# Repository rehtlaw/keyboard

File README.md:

## Build

- make sure `node` and `npm` are installed and up to date
- clone the repo
- run `npm install` inside the repo
- run `npm run gen` to regenerate the pcb file

## quirks

Ergogen's fillets are a little silly and will depending on your settings create little circles around some corners of your outline.
There doesn't seem to be any problem with just deleting them in KiCAD after the PCB generation, so just do that after running 
the generator.

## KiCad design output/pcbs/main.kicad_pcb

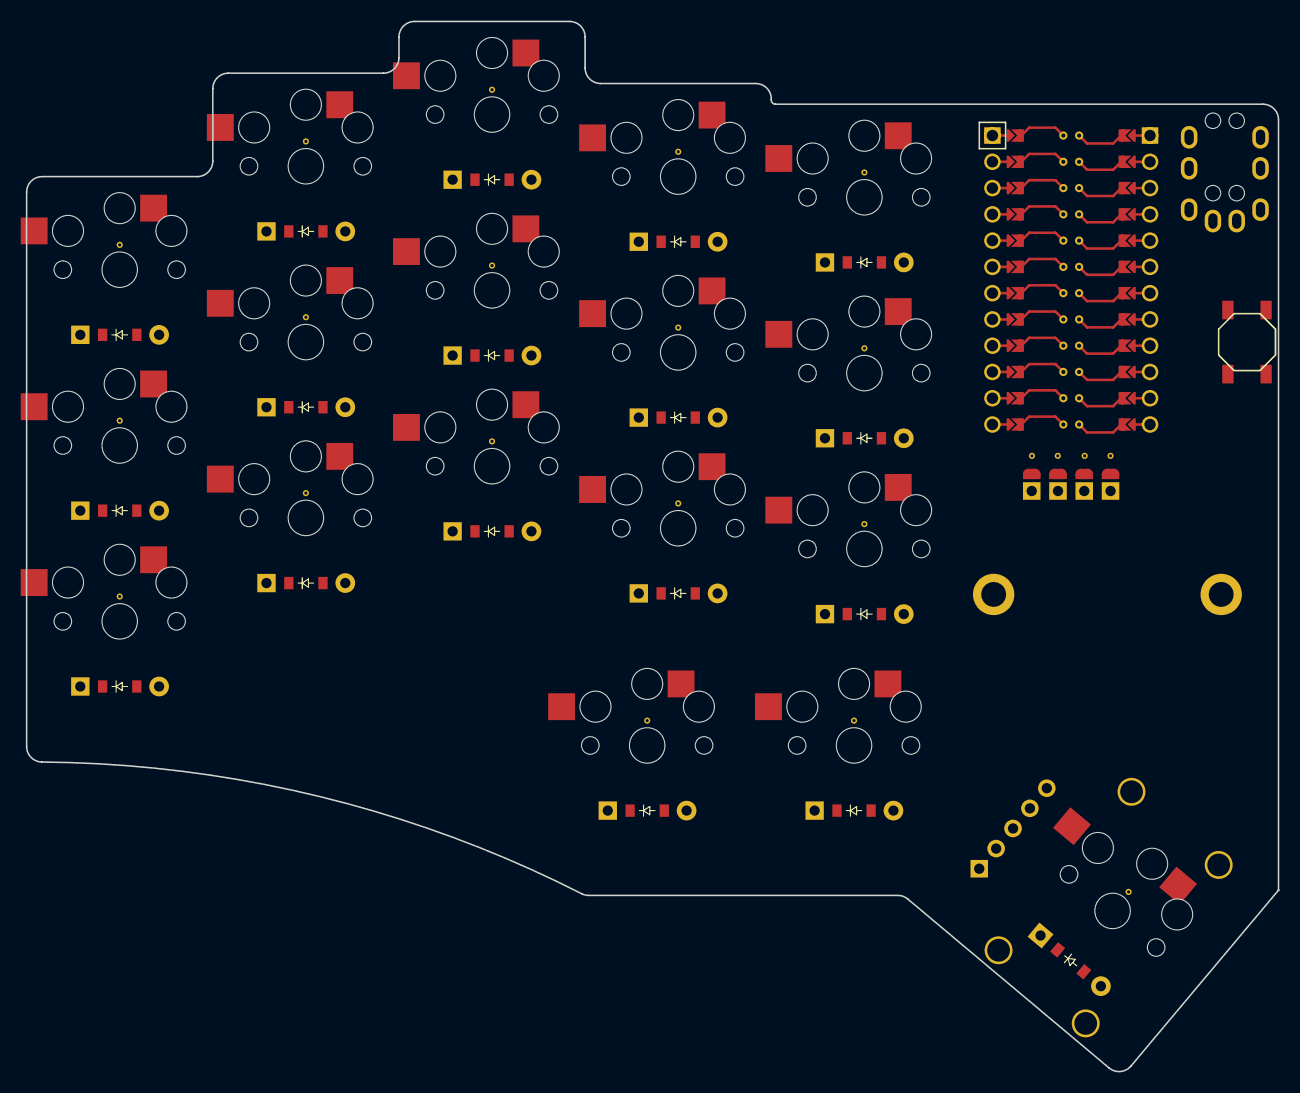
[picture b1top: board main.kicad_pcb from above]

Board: 2 copper layers, 121.0 x 101.5 mm, 44 parts (0 on the bottom side), 33 nets, no tracks yet.

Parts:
B1, B2: SW_TACT_ALPS_SKQGABE010
D1, D2, D3, D4, D5, D6, D7, D8, D9, D10, D11, D12, D13, D14, D15, D16, D17, D18: ComboDiode
Mount1: TH1; MountingHole_2.2mm_M2_DIN965_Pad
Mount2: TH2; MountingHole_2.2mm_M2_DIN965_Pad
S1, S2, S3, S4, S5, S6, S7, S8, S9, S10, S11, S12, S13, S14, S15, S16, S17, S18: PG1350
TRRS1: TRRS-PJ-320A-dual
_23: ProMicro
_24: pimoroni_trackball
_25: OLED-double-sided; OLED-128x32-double-sided

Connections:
GND: B1.1, B2.1, TRRS1.3, _23.2, _23.21, _23.22, _25.4
P0: TRRS1.4, _23.23
P2: _23.20, _25.1
P3: _23.19, _25.2
P4: D3.1, D6.1, D9.1, D12.1, D15.1, _23.18
P5: D2.1, D5.1, D8.1, D11.1, D14.1, _23.17
P6: D1.1, D4.1, D7.1, D10.1, D13.1, _23.16
P7: D16.1, D17.1, D18.1, _23.15
P14: S13.2, S14.2, S15.2, S18.2, _23.10
P15: S10.2, S11.2, S12.2, S17.2, _23.9
P18: S7.2, S8.2, S9.2, S16.2, _23.8
P19: S4.2, S5.2, S6.2, _23.7
P20: S1.2, S2.2, S3.2, _23.6
RST: B1.2, B2.2, _23.3
VCC: TRRS1.2, _23.4, _25.3
far_bottom: D13.2, S13.1
far_home: D14.2, S14.1
far_top: D15.2, S15.1
index_bottom: D10.2, S10.1
index_home: D11.2, S11.1
index_top: D12.2, S12.1
inner_main: D16.2, S16.1
middle_bottom: D7.2, S7.1
middle_home: D8.2, S8.1
middle_main: D17.2, S17.1
middle_top: D9.2, S9.1
outer_main: D18.2, S18.1
pinky_bottom: D1.2, S1.1
pinky_home: D2.2, S2.1
pinky_top: D3.2, S3.1
ring_bottom: D4.2, S4.1
ring_home: D5.2, S5.1
ring_top: D6.2, S6.1

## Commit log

2023-01-26 separate config from ergogen repo
2023-01-26 add output folder
2023-01-26 add README
2023-01-26 remove unwanted outlines
2023-01-26 ignore cache files
2023-01-26 fix PCB + add quirk to readme
2023-01-26 add more ingored files
2023-01-26 fix VCC name for oled
2023-01-26 temporary fix to turn trackball around
2023-01-26 whoops the vias were too close
2023-01-26 finished PCB, all DRC errors accounted for
2023-02-15 add some vias for each switch and the oled footprint
2023-02-15 change one of the through-holes to Mount2 for freerouting
2023-02-15 2 layer edition featuring gerber files
